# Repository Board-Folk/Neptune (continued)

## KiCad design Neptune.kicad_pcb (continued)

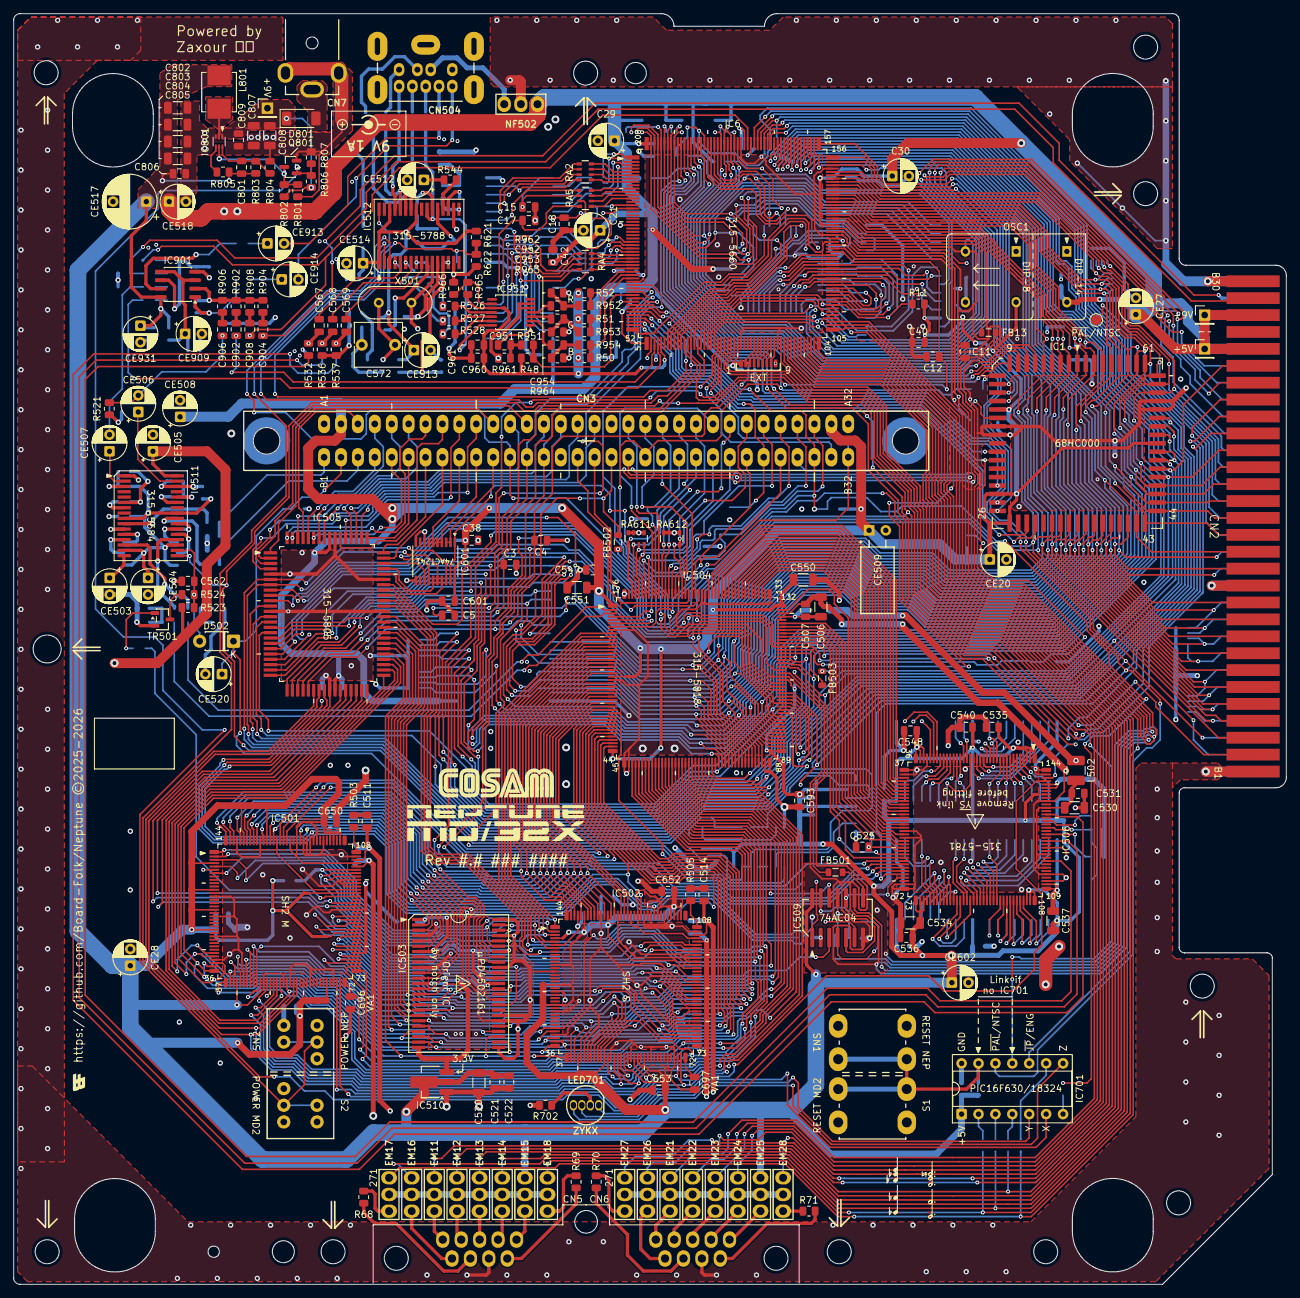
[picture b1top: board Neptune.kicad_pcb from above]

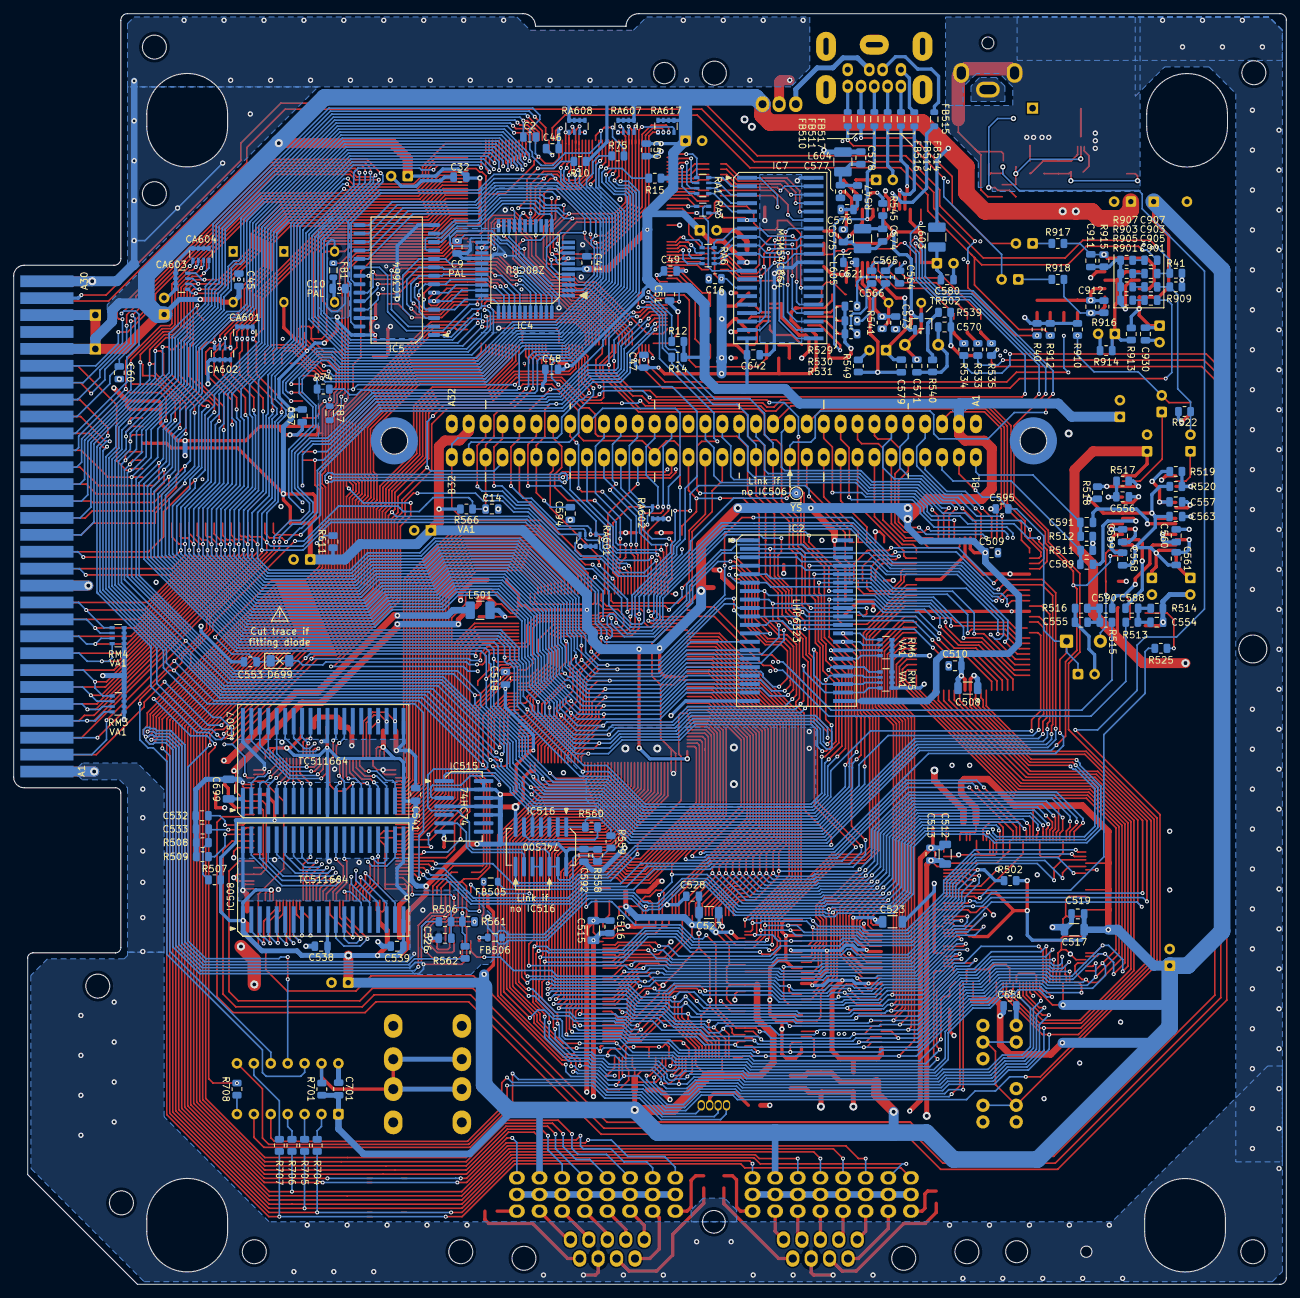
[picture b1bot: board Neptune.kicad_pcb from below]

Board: 4 copper layers, 191.2 x 190.9 mm, 379 parts (182 on the bottom side), 581 nets.

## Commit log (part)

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2025-06-02 update readme, update kicad version, add connection between 81 and GND
2025-06-02 Keep test0 pin name
2025-07-05 Region Fix Image
2025-07-05 Flex Region Fix Helper PCB
2025-09-11 Update documentation about D699, rename C695 to C553 to indicate origin (issue #7).
2025-09-11 Tie SH2 NMI pins to VCC as per original 32X main board (not obvious from schematic).
2025-11-13 Correct connection of C2 to VA21 (issue #12).
2025-11-13 Update bypass flexes for 315-5805 and 315-5818 for better connection (issue #11).
2025-11-13 Remove PAL-only designation from C11 (issue #10).
2025-11-13 Add note for C11 (issue #10).
2026-01-14 Connect controller port to PIC to support IGR (issue #13).
2026-01-15 Extend zone under controller port screw.
2026-04-27 Fix the IGR
